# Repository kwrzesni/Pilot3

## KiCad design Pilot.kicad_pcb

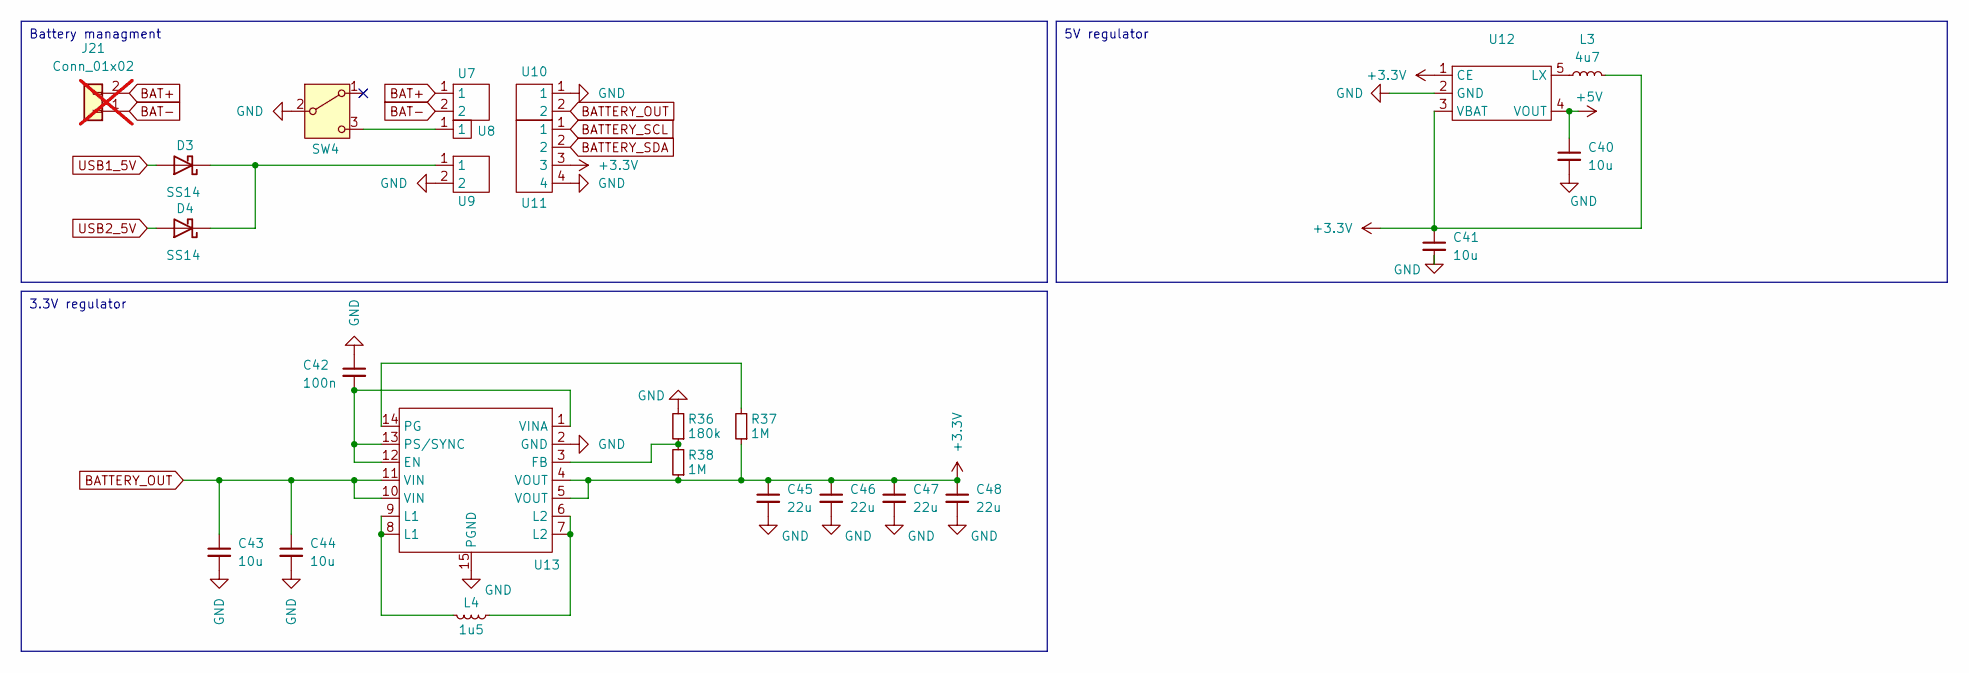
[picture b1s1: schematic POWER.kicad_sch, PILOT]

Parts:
C40, C41: 10u; C_1206_3216Metric; LCSC Part # C13585
C42: 100n; C_0402_1005Metric; LCSC Part # C147680
C43, C44: 10u; C_0603_1608Metric; LCSC Part # C466780
C45, C46, C47, C48: 22u; C_0603_1608Metric; LCSC Part # C466784
D3, D4: SS14; D_SMA; LCSC Part # C2480
J21: Conn_01x02; battery; not fitted
L3: 4u7; L_Coilcraft_XAL6060-XXX; LCSC Part # C436517
L4: 1u5; L_Vishay_IFSC-1515AH_4x4x1.8mm; LCSC Part # C3033018
R36: 180k; R_0603_1608Metric; LCSC Part # C234326
R37, R38: 1M; R_0603_1608Metric; LCSC Part # C86472
SW4: SW_SPDT; SW_SPDT_PCM12; LCSC Part # C778186
U7, U9, U10: DZ254S-11-02-48; LCSC Part # C5160785
U8: X6511WVS-01H-C60D48R2; LCSC Part # C2883758
U11: X6511WVS-04H-C60D48R1; LCSC Part # C780062
U12: SOT-25-5; LCSC Part # C2469138
U13: TPS63020DSJR; LCSC Part # C15483

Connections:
+3.3V: C41.1, C45.1, C46.1, C47.1, C48.1, L3.2, R37.1, R38.1, U11.3, U12.1 (CE), U12.3 (VBAT), U13.4 (VOUT), U13.5 (VOUT); also elsewhere on the board
+5V: C40.1, U12.4 (VOUT); also elsewhere on the board
BAT+: J21.2, U7.1
BAT-: J21.1, U7.2
BATTERY_OUT: C43.1, C44.1, U10.2, U13.10 (VIN), U13.11 (VIN)
BATTERY_SCL: U11.1; also elsewhere on the board
BATTERY_SDA: U11.2; also elsewhere on the board
GND: C40.2, C41.2, C42.1, C43.2, C44.2, C45.2, C46.2, C47.2, C48.2, R36.2, SW4.2 (B), U9.2, U10.1, U11.4, U12.2 (GND), U13.2 (GND), U13.15 (PGND); also elsewhere on the board
unnamed: D3.1 (K), D4.1 (K), U9.1
unnamed: L4.1, U13.6 (L2), U13.7 (L2)
unnamed: L4.2, U13.8 (L1), U13.9 (L1)
unnamed: SW4.3 (C), U8.1
unnamed: L3.1, U12.5 (LX)
unnamed: C42.2, U13.1 (VINA), U13.12 (EN), U13.13 (PS/SYNC)
unnamed: R36.1, R38.2, U13.3 (FB)
unnamed: R37.2, U13.14 (PG)
USB1_5V: D3.2 (A); also elsewhere on the board
USB2_5V: D4.2 (A); also elsewhere on the board

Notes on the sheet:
Battery managment
3.3V regulator
5V regulator

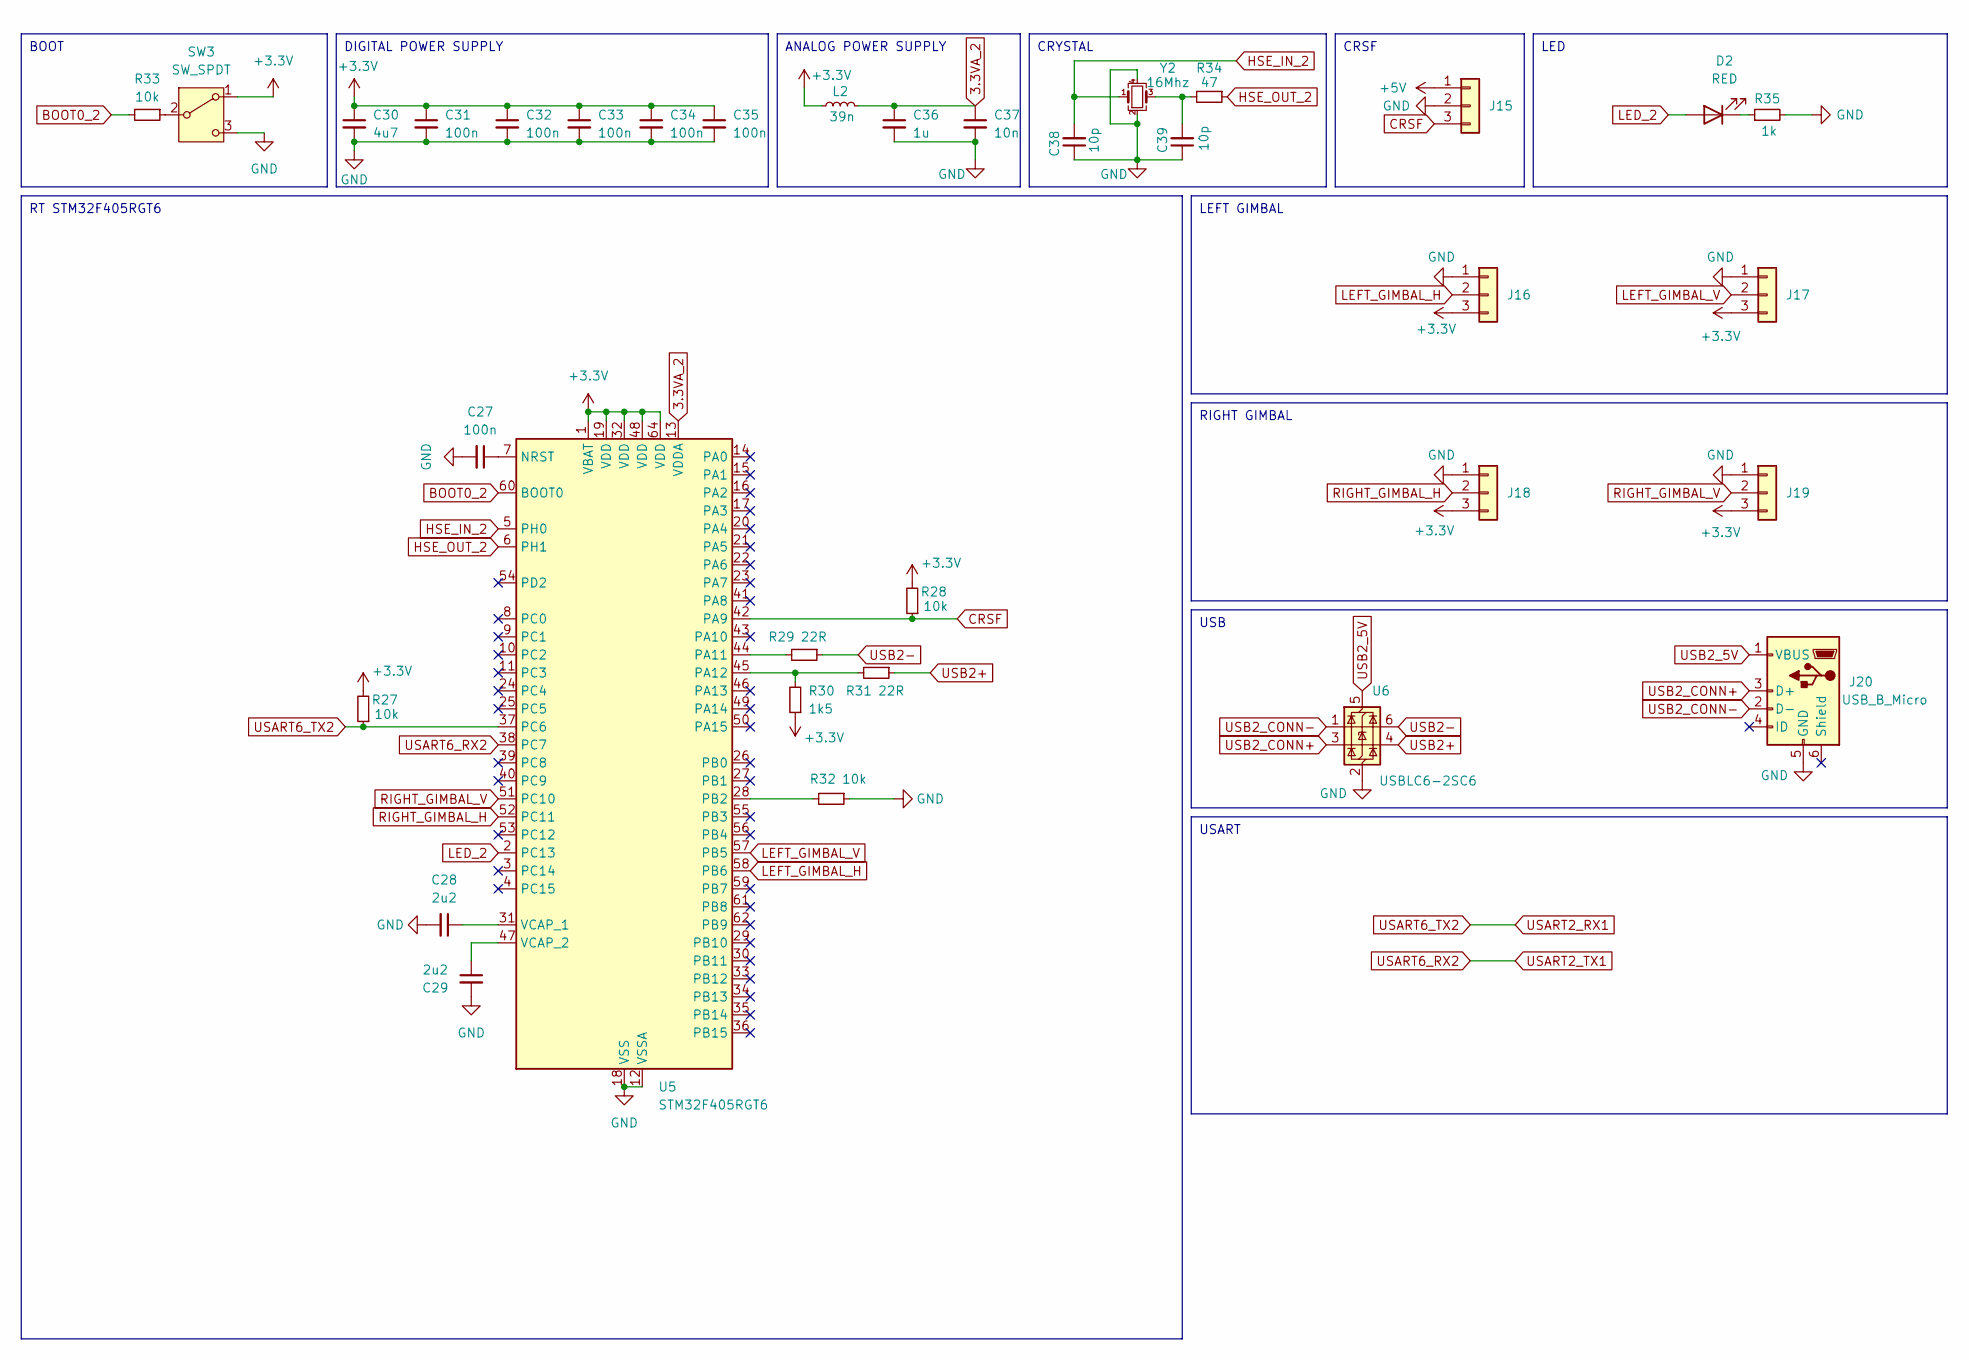
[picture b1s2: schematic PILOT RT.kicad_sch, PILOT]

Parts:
C27, C31, C32, C33, C34, C35: 100n; C_0402_1005Metric; LCSC Part # C1525
C28, C29: 2u2; C_0603_1608Metric; LCSC Part # C466784
C30: 4u7; C_0603_1608Metric; LCSC Part # C19666
C36: 1u; C_0402_1005Metric; LCSC Part # C77006
C37: 10n; C_0402_1005Metric; LCSC Part # C15195
C38, C39: 10p; C_0402_1005Metric; LCSC Part # C650948
D2: RED; D_0603_1608Metric; LCSC Part # C2286
J15: Conn_01x03; JST_ZH_B3B-ZR-SM4-TF_1x03-1MP_P1.50mm_Vertical; LCSC Part # C489717
J16, J17, J18, J19: Conn_01x03; JST_GH_BM03B-GHS-TBT_1x03-1MP_P1.25mm_Vertical; LCSC Part # C161691
J20: USB_B_Micro; USB-B micro; LCSC Part # C114094
L2: 39n; L_0402_1005Metric; LCSC Part # C408157
R27, R28, R33: 10k; R_0402_1005Metric; LCSC Part # C25744
R29, R31: 22R; R_0402_1005Metric; LCSC Part # C25092
R30: 1k5; R_0402_1005Metric; LCSC Part # C25867
R32: 10k; R_0402_1005Metric; LCSC Part # C25092
R34: 47; R_0402_1005Metric; LCSC Part # C137864
R35: 1k; R_0603_1608Metric; LCSC Part # C21190
SW3: SW_SPDT; SW_SPDT_PCM12; LCSC Part # C778186
U5: STM32F405RGT6; LQFP-64_10x10mm_P0.5mm; LCSC Part # C15742
U6: USBLC6-2SC6; SOT-23-6; LCSC Part # C2827654
Y2: 16Mhz; Crystal_SMD_3225-4Pin_3.2x2.5mm; LCSC Part # C13738

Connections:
3.3VA_2: C36.1, C37.1, L2.2, U5.13 (VDDA)
+3.3V: C30.1, C31.1, C32.1, C33.1, C34.1, C35.1, J16.3, J17.3, J18.3, J19.3, L2.1, R27.2, R28.2, R30.1, SW3.1 (A), U5.1 (VBAT), U5.19 (VDD), U5.32 (VDD), U5.48 (VDD), U5.64 (VDD); also elsewhere on the board
+5V: J15.1; also elsewhere on the board
BOOT0_2: R33.2, U5.60 (BOOT0)
CRSF: J15.3, R28.1, U5.42 (PA9)
GND: C27.2, C28.2, C29.2, C30.2, C31.2, C32.2, C33.2, C34.2, C35.2, C36.2, C37.2, C38.1, C39.1, J15.2, J16.1, J17.1, J18.1, J19.1, J20.5 (GND), R32.1, R35.2, SW3.3 (C), U5.12 (VSSA), U5.18 (VSS), U5.63 (VSS), U6.2 (GND), Y2.2, Y2.4; also elsewhere on the board
HSE_IN_2: C38.2, U5.5 (PH0), Y2.1
HSE_OUT_2: R34.1, U5.6 (PH1)
LED_2: D2.2 (A), U5.2 (PC13)
LEFT_GIMBAL_H: J16.2, U5.58 (PB6)
LEFT_GIMBAL_V: J17.2, U5.57 (PB5)
unnamed: C39.2, R34.2, Y2.3
unnamed: D2.1 (K), R35.1
unnamed: R33.1, SW3.2 (B)
unnamed: C27.1, U5.7 (NRST)
unnamed: R29.2, U5.44 (PA11)
unnamed: R30.2, R31.2, U5.45 (PA12)
unnamed: R32.2, U5.28 (PB2)
unnamed: C28.1, U5.31 (VCAP_1)
unnamed: C29.1, U5.47 (VCAP_2)
RIGHT_GIMBAL_H: J18.2, U5.52 (PC11)
RIGHT_GIMBAL_V: J19.2, U5.51 (PC10)
USART2_RX1: R27.1, U5.37 (PC6); also elsewhere on the board
USART2_TX1: U5.38 (PC7); also elsewhere on the board
USB2+: R31.1, U6.4 (I/O2)
USB2-: R29.1, U6.6 (I/O1)
USB2_5V: J20.1 (VBUS), U6.5 (VBUS); also elsewhere on the board
USB2_CONN+: J20.3 (D+), U6.3 (I/O2)
USB2_CONN-: J20.2 (D-), U6.1 (I/O1)

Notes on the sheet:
USB
CRSF
RIGHT GIMBAL
LEFT GIMBAL
CRYSTAL
BOOT
LED
ANALOG POWER SUPPLY
USART
DIGITAL POWER SUPPLY
RT STM32F405RGT6

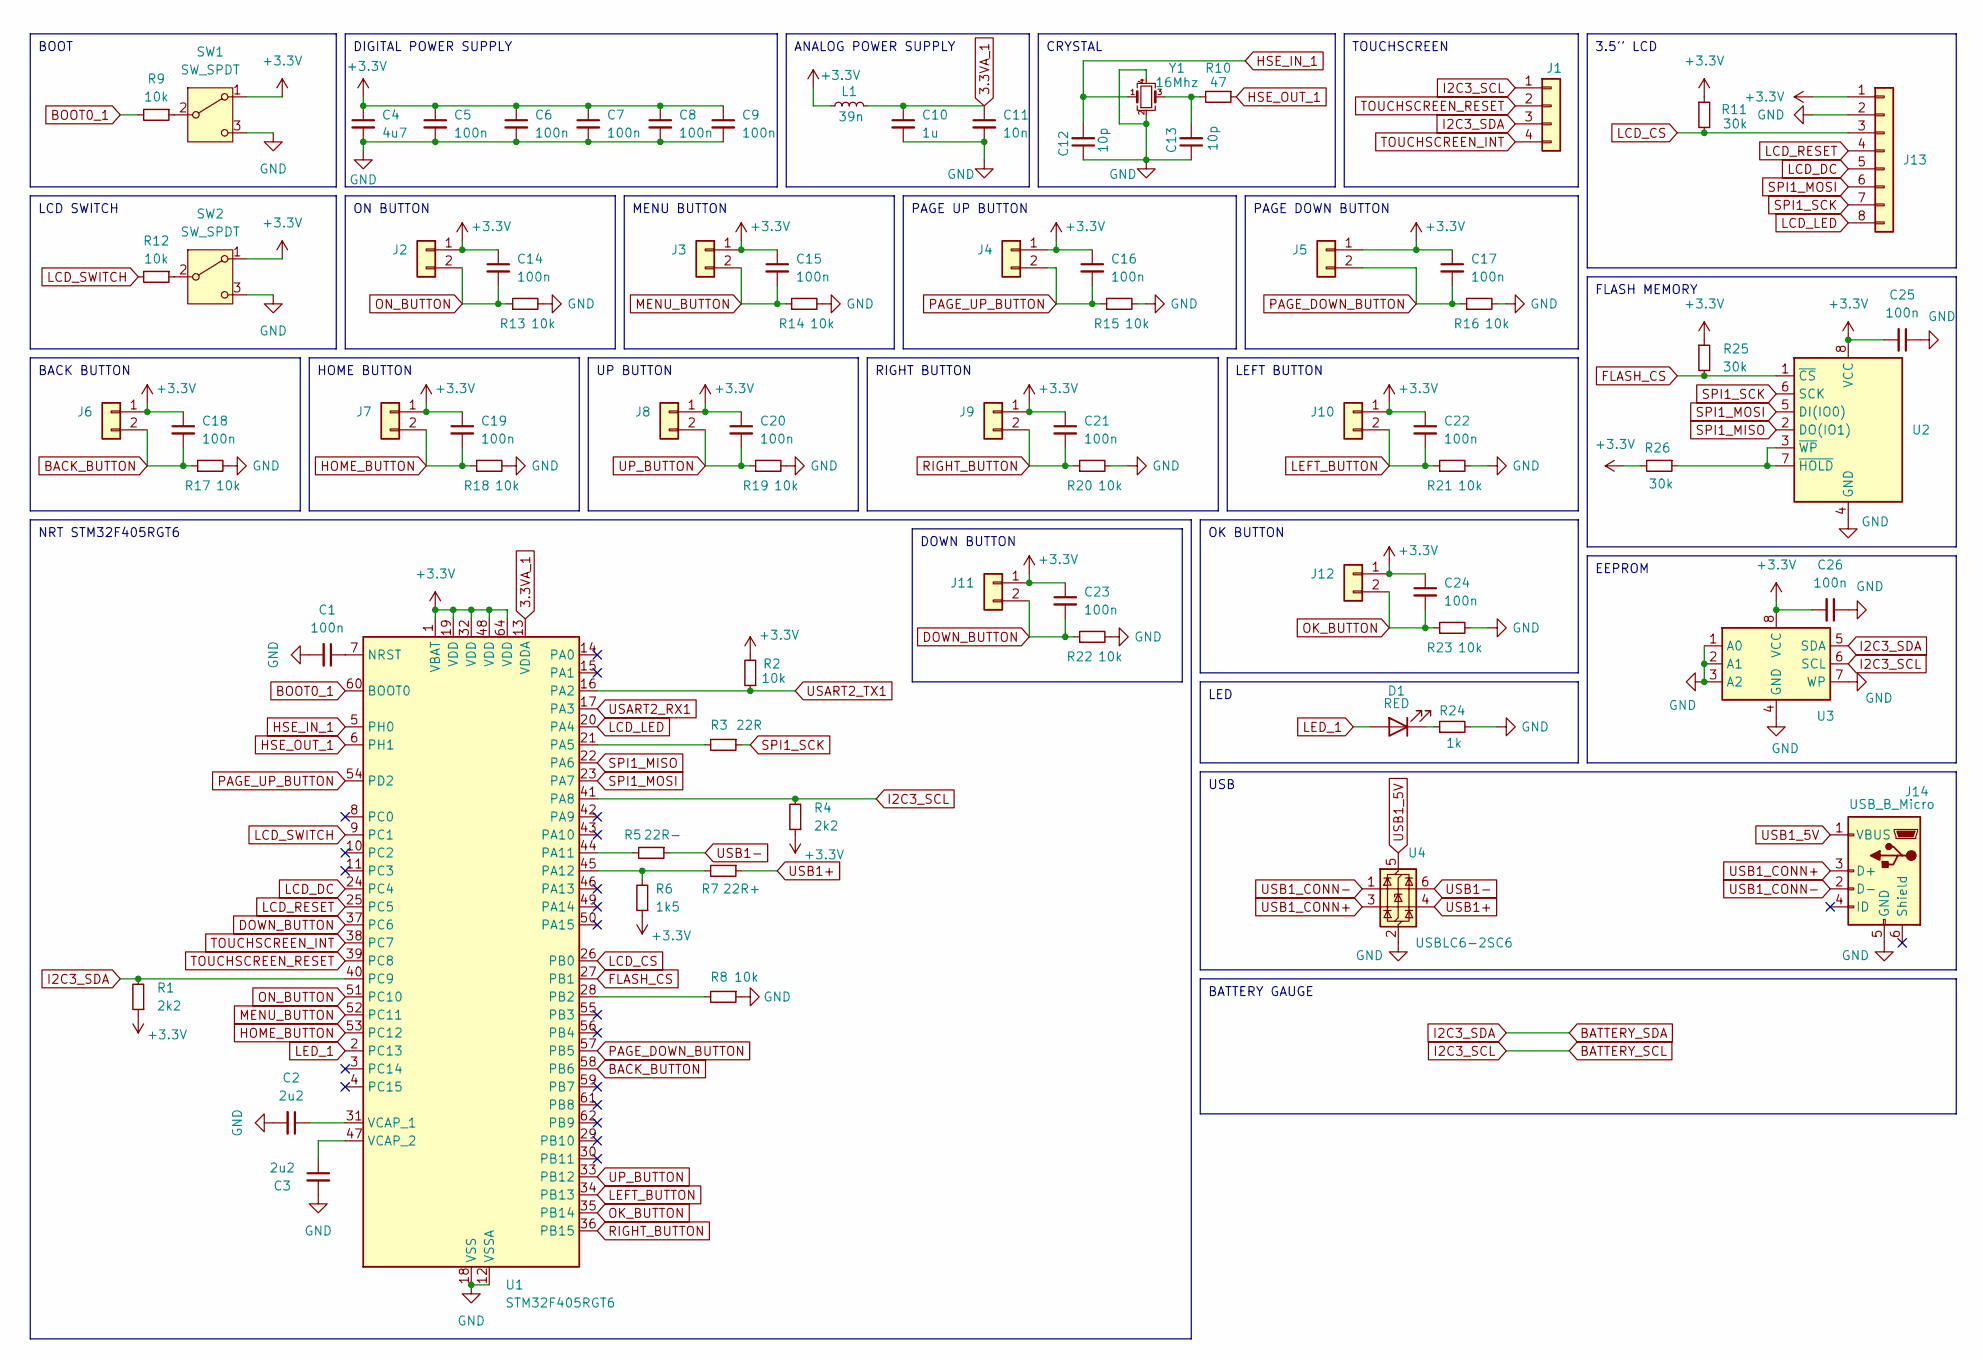
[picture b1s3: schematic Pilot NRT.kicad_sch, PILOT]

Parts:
C1, C5, C6, C7, C8, C9, C14, C15, C16, C17, C18, C19, C20, C21, C22, C23, C24, C25, C26: 100n; C_0402_1005Metric; LCSC Part # C1525
C2, C3: 2u2; C_0603_1608Metric; LCSC Part # C466784
C4: 4u7; C_0603_1608Metric; LCSC Part # C19666
C10: 1u; C_0402_1005Metric; LCSC Part # C77006
C11: 10n; C_0402_1005Metric; LCSC Part # C15195
C12, C13: 10p; C_0402_1005Metric; LCSC Part # C650948
D1: RED; D_0603_1608Metric; LCSC Part # C2286
J1: Touchscreen; JST_GH_BM04B-GHS-TBT_1x04-1MP_P1.25mm_Vertical; LCSC Part # C161692
J2, J3, J4, J5, J6, J7, J8, J9, J10, J11, J12: Conn_01x02; JST_GH_BM02B-GHS-TBT_1x02-1MP_P1.25mm_Vertical; LCSC Part # C161690
J13: 3.5'' LCD; JST_ZH_B8B-ZR-SM4-TF_1x08-1MP_P1.50mm_Vertical; LCSC Part # C265368
J14: USB_B_Micro; USB-B micro; LCSC Part # C114094
L1: 39n; L_0402_1005Metric; LCSC Part # C408157
R1, R4: 2k2; R_0402_1005Metric; LCSC Part # C25879
R2, R9, R12, R13, R14, R15, R16, R17, R18, R19, R20, R21, R22, R23: 10k; R_0402_1005Metric; LCSC Part # C25744
R3: 22R; R_0402_1005Metric; LCSC Part # C25092
R5: 22R-; R_0402_1005Metric; LCSC Part # C25092
R6: 1k5; R_0402_1005Metric; LCSC Part # C25867
R7: 22R+; R_0402_1005Metric; LCSC Part # C25092
R8: 10k; R_0402_1005Metric; LCSC Part # C25092
R10: 47; R_0402_1005Metric; LCSC Part # C137864
R11, R25, R26: 30k; R_0603_1608Metric; LCSC Part # C22984
R24: 1k; R_0603_1608Metric; LCSC Part # C21190
SW1, SW2: SW_SPDT; SW_SPDT_PCM12; LCSC Part # C778186
U1: STM32F405RGT6; LQFP-64_10x10mm_P0.5mm; LCSC Part # C15742
U2: W25X40CLSS; SOIC-8_5.275x5.275mm_P1.27mm; LCSC Part # C97521
U3: AT24CS01-XHM; SOP-8_3.9x4.9mm_P1.27mm; LCSC Part # C918274
U4: USBLC6-2SC6; SOT-23-6; LCSC Part # C2827654
Y1: 16Mhz; Crystal_SMD_3225-4Pin_3.2x2.5mm; LCSC Part # C13738

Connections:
3.3VA_1: C10.1, C11.1, L1.2, U1.13 (VDDA)
+3.3V: C4.1, C5.1, C6.1, C7.1, C8.1, C9.1, C14.1, C15.1, C16.1, C17.1, C18.1, C19.1, C20.1, C21.1, C22.1, C23.1, C24.1, C25.2, C26.2, J2.1, J3.1, J4.1, J5.1, J6.1, J7.1, J8.1, J9.1, J10.1, J11.1, J12.1, J13.1, L1.1, R1.1, R2.2, R4.1, R6.1, R11.1, R25.1, R26.2, SW1.1 (A), SW2.1 (A), U1.1 (VBAT), U1.19 (VDD), U1.32 (VDD), U1.48 (VDD), U1.64 (VDD), U2.8 (VCC), U3.8 (VCC); also elsewhere on the board
BACK_BUTTON: C18.2, J6.2, R17.1, U1.58 (PB6)
BATTERY_SCL: J1.1, R4.2, U1.41 (PA8), U3.6 (SCL); also elsewhere on the board
BATTERY_SDA: J1.3, R1.2, U1.40 (PC9), U3.5 (SDA); also elsewhere on the board
BOOT0_1: R9.2, U1.60 (BOOT0)
DOWN_BUTTON: C23.2, J11.2, R22.1, U1.37 (PC6)
FLASH_CS: R25.2, U1.27 (PB1), U2.1 (~CS)
GND: C1.2, C2.2, C3.2, C4.2, C5.2, C6.2, C7.2, C8.2, C9.2, C10.2, C11.2, C12.1, C13.1, C25.1, C26.1, J13.2, J14.5 (GND), R8.1, R13.2, R14.2, R15.2, R16.2, R17.2, R18.2, R19.2, R20.2, R21.2, R22.2, R23.2, R24.2, SW1.3 (C), SW2.3 (C), U1.12 (VSSA), U1.18 (VSS), U1.63 (VSS), U2.4 (GND), U3.1 (A0), U3.2 (A1), U3.3 (A2), U3.4 (GND), U3.7 (WP), U4.2 (GND), Y1.2, Y1.4; also elsewhere on the board
HOME_BUTTON: C19.2, J7.2, R18.1, U1.53 (PC12)
HSE_IN_1: C12.2, U1.5 (PH0), Y1.1
HSE_OUT_1: R10.1, U1.6 (PH1)
LCD_CS: J13.3, R11.2, U1.26 (PB0)
LCD_DC: J13.5, U1.24 (PC4)
LCD_LED: J13.8, U1.20 (PA4)
LCD_RESET: J13.4, U1.25 (PC5)
LCD_SWITCH: R12.2, U1.9 (PC1)
LED_1: D1.2 (A), U1.2 (PC13)
LEFT_BUTTON: C22.2, J10.2, R21.1, U1.34 (PB13)
MENU_BUTTON: C15.2, J3.2, R14.1, U1.52 (PC11)
unnamed: C13.2, R10.2, Y1.3
unnamed: D1.1 (K), R24.1
unnamed: R9.1, SW1.2 (B)
unnamed: R12.1, SW2.2 (B)
unnamed: C1.1, U1.7 (NRST)
unnamed: R3.2, U1.21 (PA5)
unnamed: R5.2, U1.44 (PA11)
unnamed: R6.2, R7.2, U1.45 (PA12)
unnamed: R8.2, U1.28 (PB2)
unnamed: C2.1, U1.31 (VCAP_1)
unnamed: C3.1, U1.47 (VCAP_2)
unnamed: R26.1, U2.3 (~WP), U2.7 (~HOLD)
OK_BUTTON: C24.2, J12.2, R23.1, U1.35 (PB14)
ON_BUTTON: C14.2, J2.2, R13.1, U1.51 (PC10)
PAGE_DOWN_BUTTON: C17.2, J5.2, R16.1, U1.57 (PB5)
PAGE_UP_BUTTON: C16.2, J4.2, R15.1, U1.54 (PD2)
RIGHT_BUTTON: C21.2, J9.2, R20.1, U1.36 (PB15)
SPI1_MISO: U1.22 (PA6), U2.2 (DO(IO1))
SPI1_MOSI: J13.6, U1.23 (PA7), U2.5 (DI(IO0))
SPI1_SCK: J13.7, R3.1, U2.6 (SCK)
TOUCHSCREEN_INT: J1.4, U1.38 (PC7)
TOUCHSCREEN_RESET: J1.2, U1.39 (PC8)
UP_BUTTON: C20.2, J8.2, R19.1, U1.33 (PB12)
USART2_RX1: U1.17 (PA3); also elsewhere on the board
USART2_TX1: R2.1, U1.16 (PA2); also elsewhere on the board
USB1+: R7.1, U4.4 (I/O2)
USB1-: R5.1, U4.6 (I/O1)
USB1_5V: J14.1 (VBUS), U4.5 (VBUS); also elsewhere on the board
USB1_CONN+: J14.3 (D+), U4.3 (I/O2)
USB1_CONN-: J14.2 (D-), U4.1 (I/O1)

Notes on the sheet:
ANALOG POWER SUPPLY
BACK BUTTON
DIGITAL POWER SUPPLY
LEFT BUTTON
ON BUTTON
PAGE UP BUTTON
USB
3.5'' LCD
FLASH MEMORY
MENU BUTTON
DOWN BUTTON
PAGE DOWN BUTTON
RIGHT BUTTON
NRT STM32F405RGT6
HOME BUTTON
BATTERY GAUGE
UP BUTTON
EEPROM
TOUCHSCREEN
LED
CRYSTAL
LCD SWITCH
BOOT
OK BUTTON

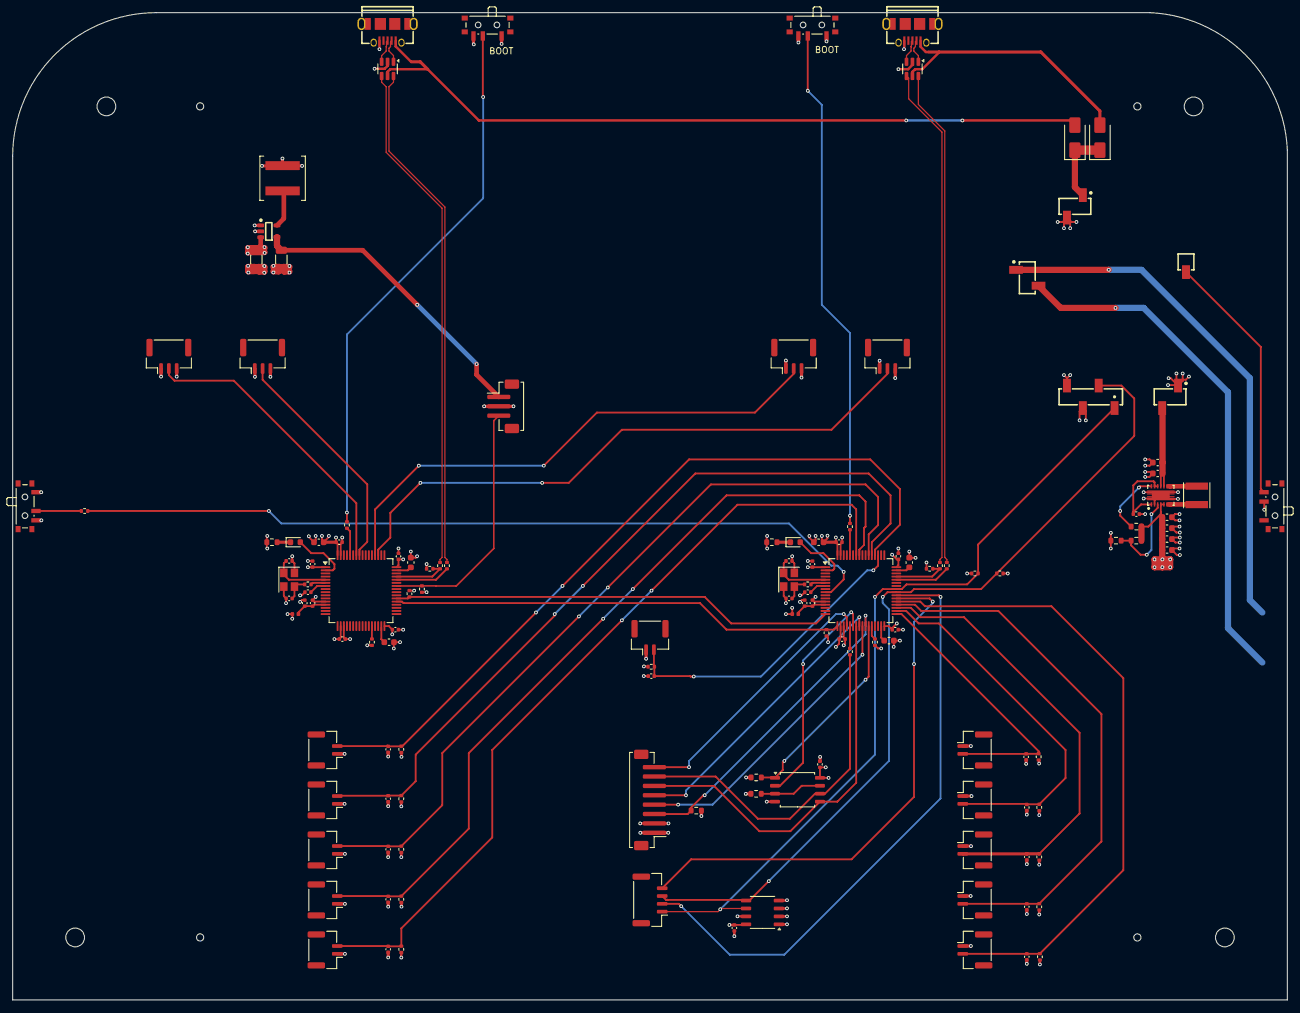
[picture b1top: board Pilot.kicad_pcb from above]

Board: 4 copper layers, 204.0 x 158.0 mm, 134 parts (0 on the bottom side), 86 nets.

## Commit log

2024-06-17 add version control to Pilot3 project
2024-06-17 add material list
2024-06-19 rouch parts placement
2024-06-21 first wiring
2024-06-23 gerber files
2024-06-23 fix wrong footprints
2024-07-19 update to STM32F04
